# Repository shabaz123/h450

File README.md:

# h450
H450 Motor Tools

The h450-motor-example.ino file can be used as an example of how the H450 (TB67H450FNG) motor driver board can be used.

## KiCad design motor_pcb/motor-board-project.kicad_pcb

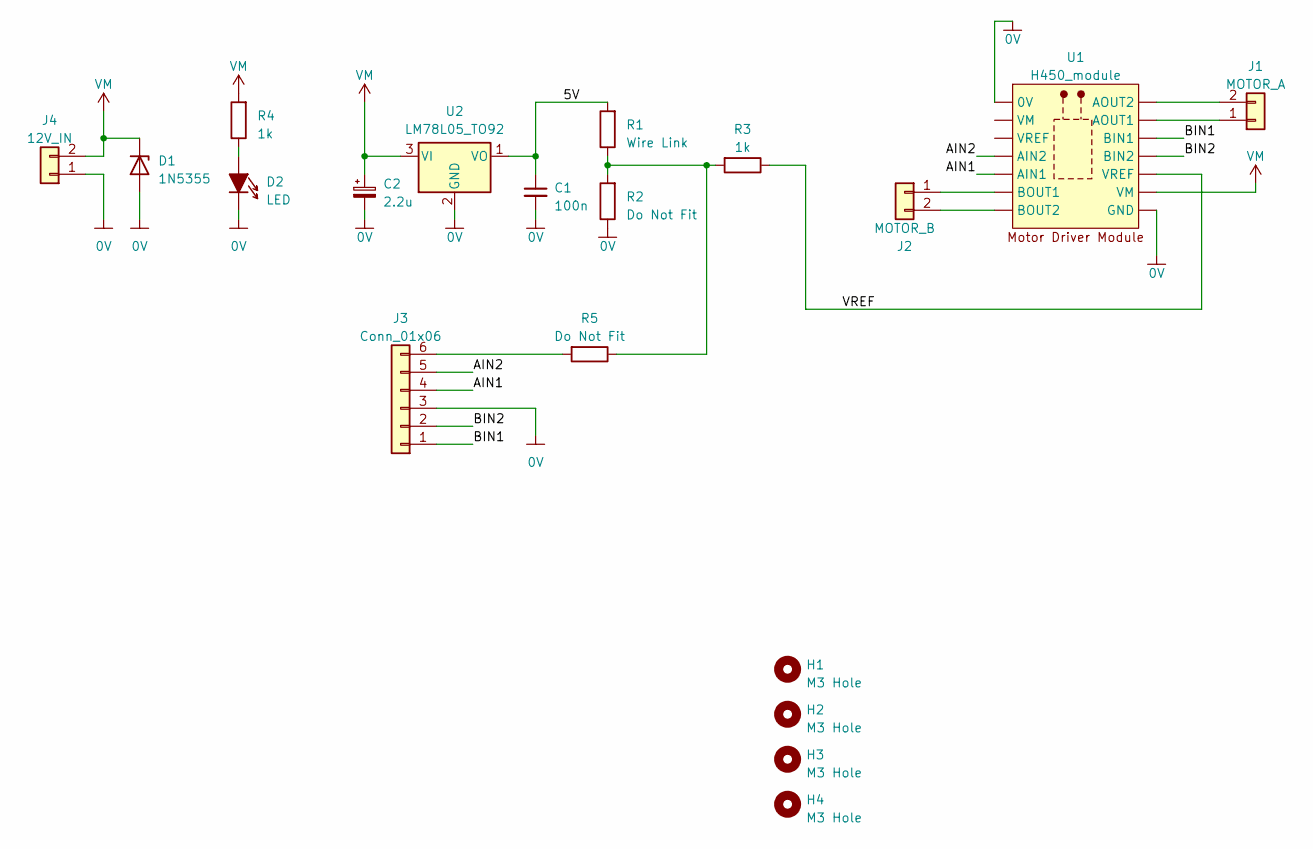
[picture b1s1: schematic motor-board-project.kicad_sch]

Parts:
C1: 100n; C_Axial_L3.8mm_D2.6mm_P7.50mm_Horizontal
C2: 2.2u; CP_Radial_D5.0mm_P2.50mm
D1: 1N5355; D_DO-201AE_P12.70mm_Horizontal
D2: LED; LED_5mm
H1, H2, H3, H4: M3 Hole; HOLE_BARE_3.1mm
J1: MOTOR_A; TerminalBlock_2way-3.5-3.81mm
J2: MOTOR_B; TerminalBlock_2way-3.5-3.81mm
J3: Conn_01x06; PinHeader_1x06_P2.54mm_Vertical
J4: 12V_IN; TerminalBlock_2way-3.5-3.81mm
R1: Wire Link; R_Axial_DIN0207_L6.3mm_D2.5mm_P10.16mm_Horizontal
R2, R5: Do Not Fit; R_Axial_DIN0207_L6.3mm_D2.5mm_P10.16mm_Horizontal
R3, R4: 1k; R_Axial_DIN0207_L6.3mm_D2.5mm_P10.16mm_Horizontal
U1: H450_module; H450-module
U2: LM78L05_TO92; TO-92_Wide

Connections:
0V: C1.2, C2.2, D1.2 (A), D2.1 (K), J3.3, J4.1, R2.1, U1.1 (0V), U1.8 (GND), U2.2 (GND)
/5V: C1.1, R1.2, U2.1 (VO)
/AIN1: J3.4, U1.5 (AIN1)
/AIN2: J3.5, U1.4 (AIN2)
/BIN1: J3.1, U1.12 (BIN1)
/BIN2: J3.2, U1.11 (BIN2)
/VREF: R3.1, U1.10 (VREF)
unnamed: D2.2 (A), R4.1
unnamed: J1.1, U1.13 (AOUT1)
unnamed: J1.2, U1.14 (AOUT2)
unnamed: J2.1, U1.6 (BOUT1)
unnamed: J2.2, U1.7 (BOUT2)
unnamed: J3.6, R5.2
unnamed: R1.1, R2.2, R3.2, R5.1
VM: C2.1, D1.1 (K), J4.2, R4.2, U1.9 (VM), U2.3 (VI)

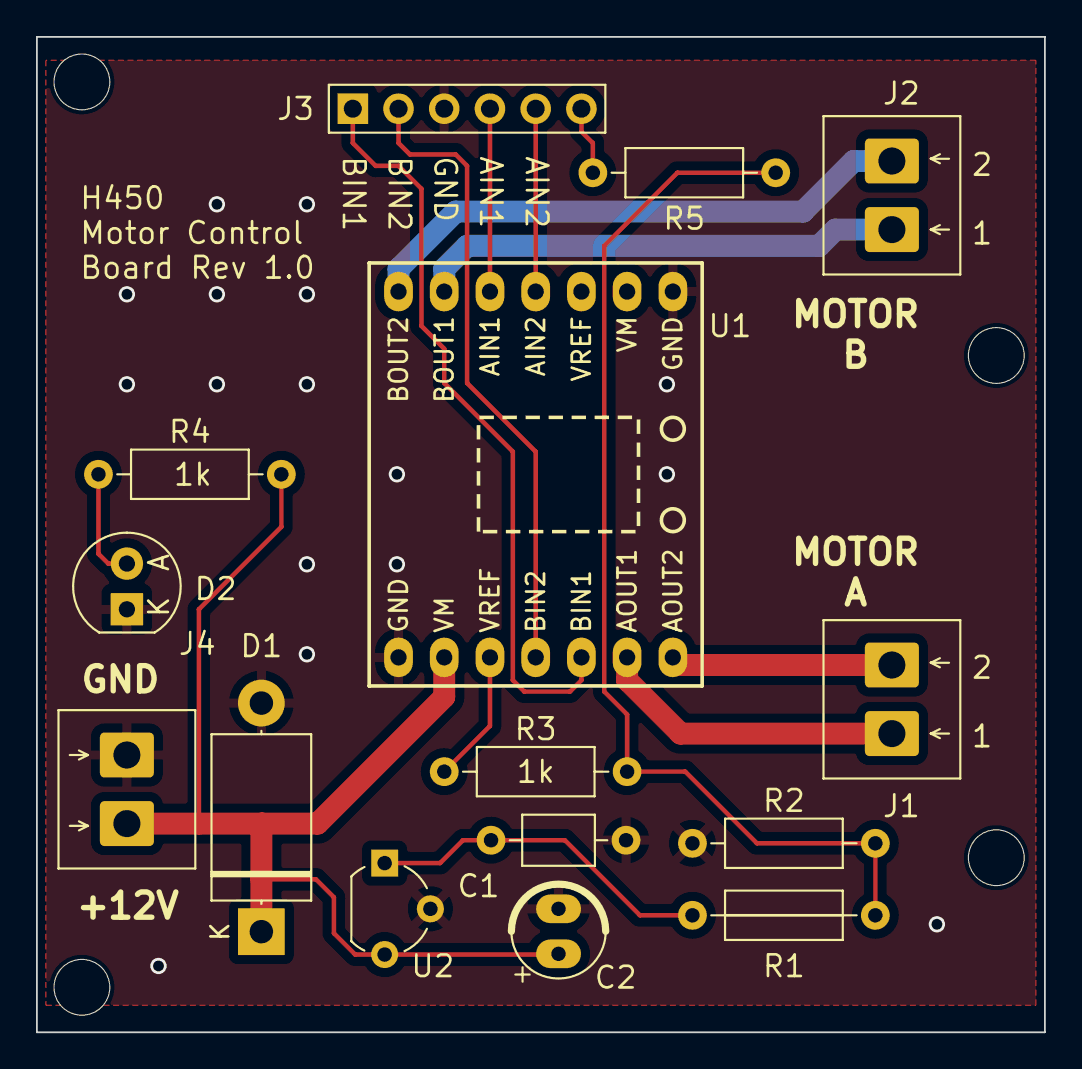
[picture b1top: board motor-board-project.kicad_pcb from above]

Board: 2 copper layers, 56.0 x 55.3 mm, 19 parts (0 on the bottom side), 15 nets.

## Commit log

2023-09-15 Arduino Library implememtation
2023-09-15 Corrected typo
